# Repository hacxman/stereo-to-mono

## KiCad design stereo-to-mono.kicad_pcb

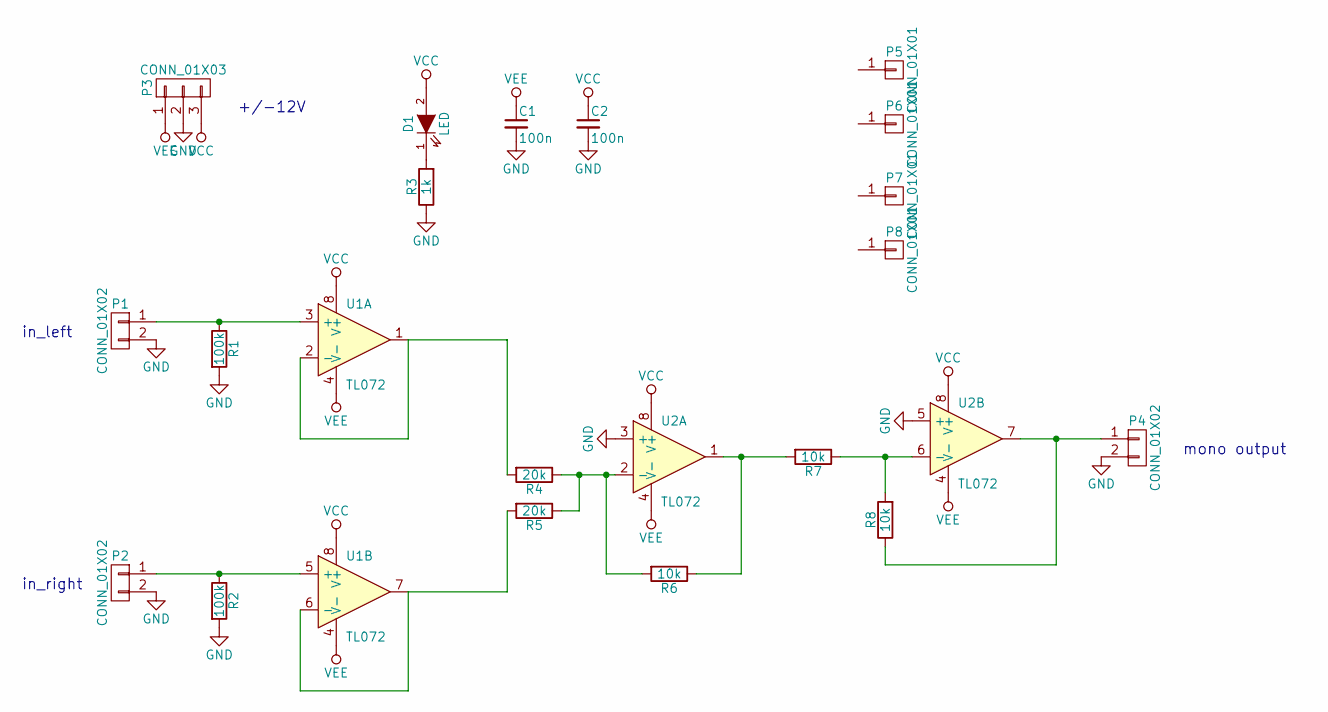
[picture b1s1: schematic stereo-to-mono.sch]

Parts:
C1, C2: 100n; C_Rect_L7_W2.5_P5
D1: LED; LED_1206
P1, P2, P4: CONN_01X02; TerminalBlock_Pheonix_MKDS1.5-2pol
P3: CONN_01X03; TerminalBlock_Pheonix_MKDS1.5-3pol
P5, P6, P7, P8: CONN_01X01; MountingHole_3mm
R1, R2: 100k; Resistor_Horizontal_RM10mm
R3: 1k; R_0603_HandSoldering
R4, R5: 20k; Resistor_Horizontal_RM10mm
R6, R7, R8: 10k; Resistor_Horizontal_RM10mm
U1, U2: TL072; DIP-8_W7.62mm_LongPads

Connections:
GND: C1.2, C2.2, P1.2, P2.2, P3.2, P4.2, R1.2, R2.2, R3.1, U2.3 (+), U2.5 (+)
unnamed: D1.1 (K), R3.2
unnamed: P1.1, R1.1, U1.3 (+)
unnamed: P2.1, R2.1, U1.5 (+)
unnamed: P4.1, R8.1, U2.7
unnamed: R4.1, R5.1, R6.2, U2.2 (-)
unnamed: R4.2, U1.1, U1.2 (-)
unnamed: R5.2, U1.6 (-), U1.7
unnamed: R6.1, R7.2, U2.1
unnamed: R7.1, R8.2, U2.6 (-)
VCC: C2.1, D1.2 (A), P3.3, U1.8 (V+), U2.8 (V+)
VEE: C1.1, P3.1, U1.4 (V-), U2.4 (V-)

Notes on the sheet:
in_left
in_right
mono output
+/-12V

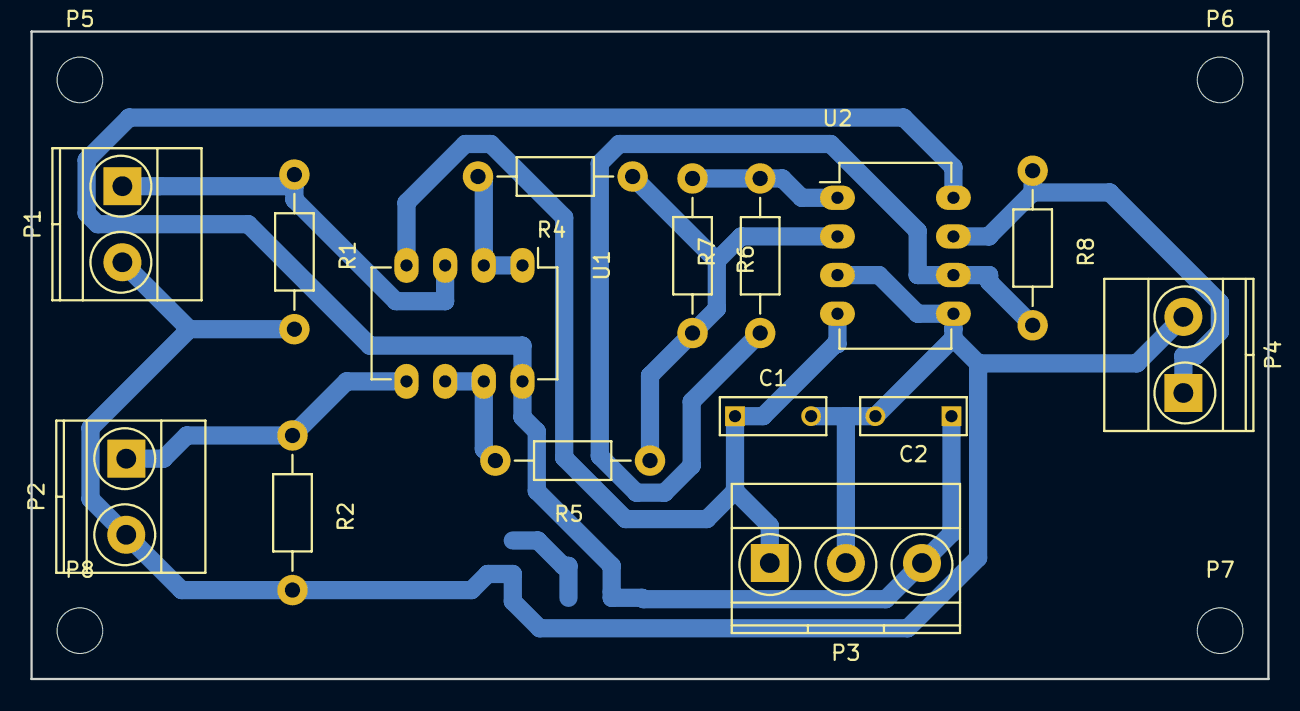
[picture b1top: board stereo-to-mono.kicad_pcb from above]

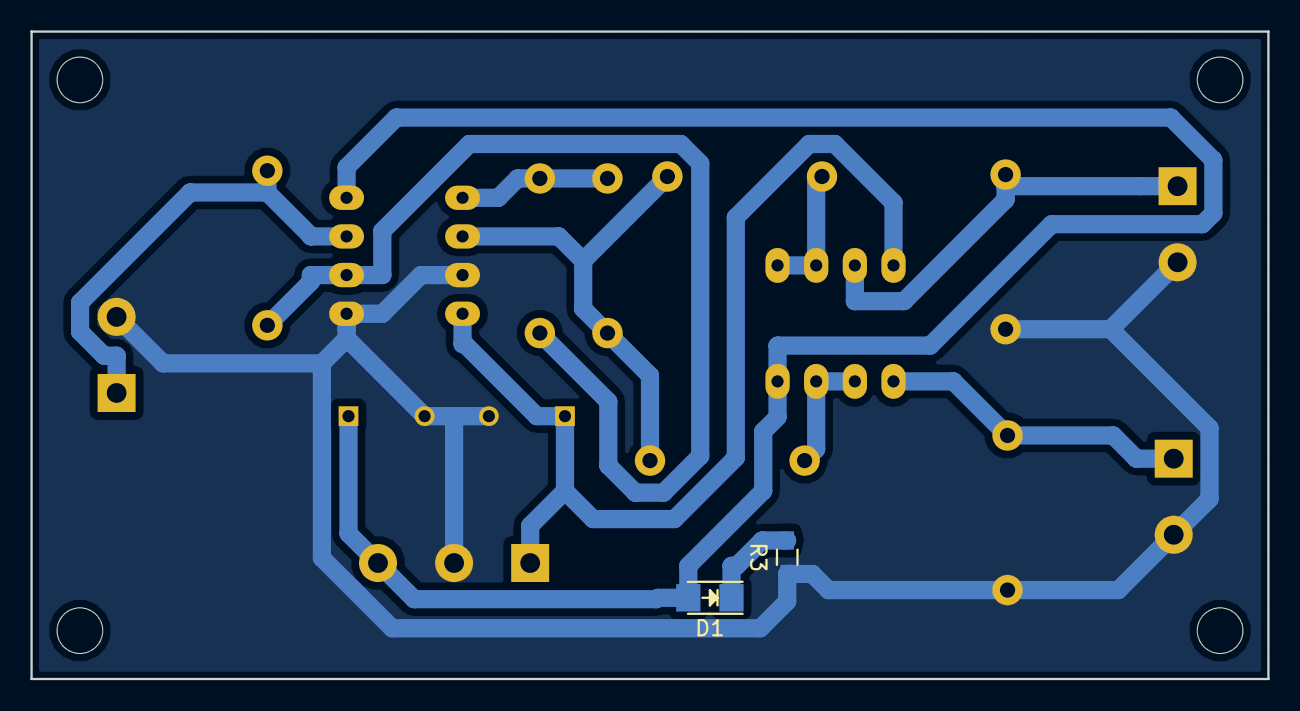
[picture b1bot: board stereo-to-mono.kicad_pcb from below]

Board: 2 copper layers, 81.3 x 42.5 mm, 21 parts (2 on the bottom side), 12 nets.

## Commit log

2016-09-01 first
